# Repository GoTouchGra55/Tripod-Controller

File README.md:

# Tripod (Controller)
A device that works as the brains of a tri-legged hopping robot!

## Overview
Tripod-controller is a 4 layer printed circuit board which is to be used as the computing and instructory brains of a major robot project I've been working on.

The board handles the robot's main control electronics, providing the necessary computing capabilities for its various subsystems both planned and unplanned.

## Design

SEE [SCHEMATICS](KiCAD/Controller.pdf)

## Build Instructions
1. Order the PCB using the provided [files](KiCAD/production).
2. Solder all SMD components according to the schematic and PCB layout.
3. Inspect all solder joints and check for shorts.
4. Connect the peripherals according to the schematic.
5. Flash the firmware and verify all interfaces.
6. Test the power rails before connecting the motors.

## BOM
| Category | Item | Quantity | Supplier | Unit Cost (USD) | Total Cost (USD) | Notes |
|---|---|---:|---|---:|---:|---|
| PCB manufacturing | JLCPCB order | 1 | JLCPCB | $134.68 | $134.68 | JLCPCB order subtotal |
| Shipping | FedEx shipping | 1 | FedEx | $27.19 | $27.19 | Included in the quoted JLCPCB total |
| Passive components | SMD resistors | As required | Daraz | $0.00 | $0.00 | Already owned |
| Passive components | SMD capacitors | As required | Daraz | $0.00 | $0.00 | Already owned |
| **TOTAL** |  |  |  |  | **$161.87** |  |

### SEE [BOM](BOM.csv)

## IMPORTANT
1. Use a 3-4s LiPo battery if you decide to use this board in your project. Discard the battery if it smells "funny".

2. Check for any damage on the pcb as it can be the reason for a catastrophic failure.

## License
MIT-License - SEE [LICENSE](LICENSE)

## Author
Shaurya Tamang  
Contact: [Email](shauryatamand.dev@gmail.com)

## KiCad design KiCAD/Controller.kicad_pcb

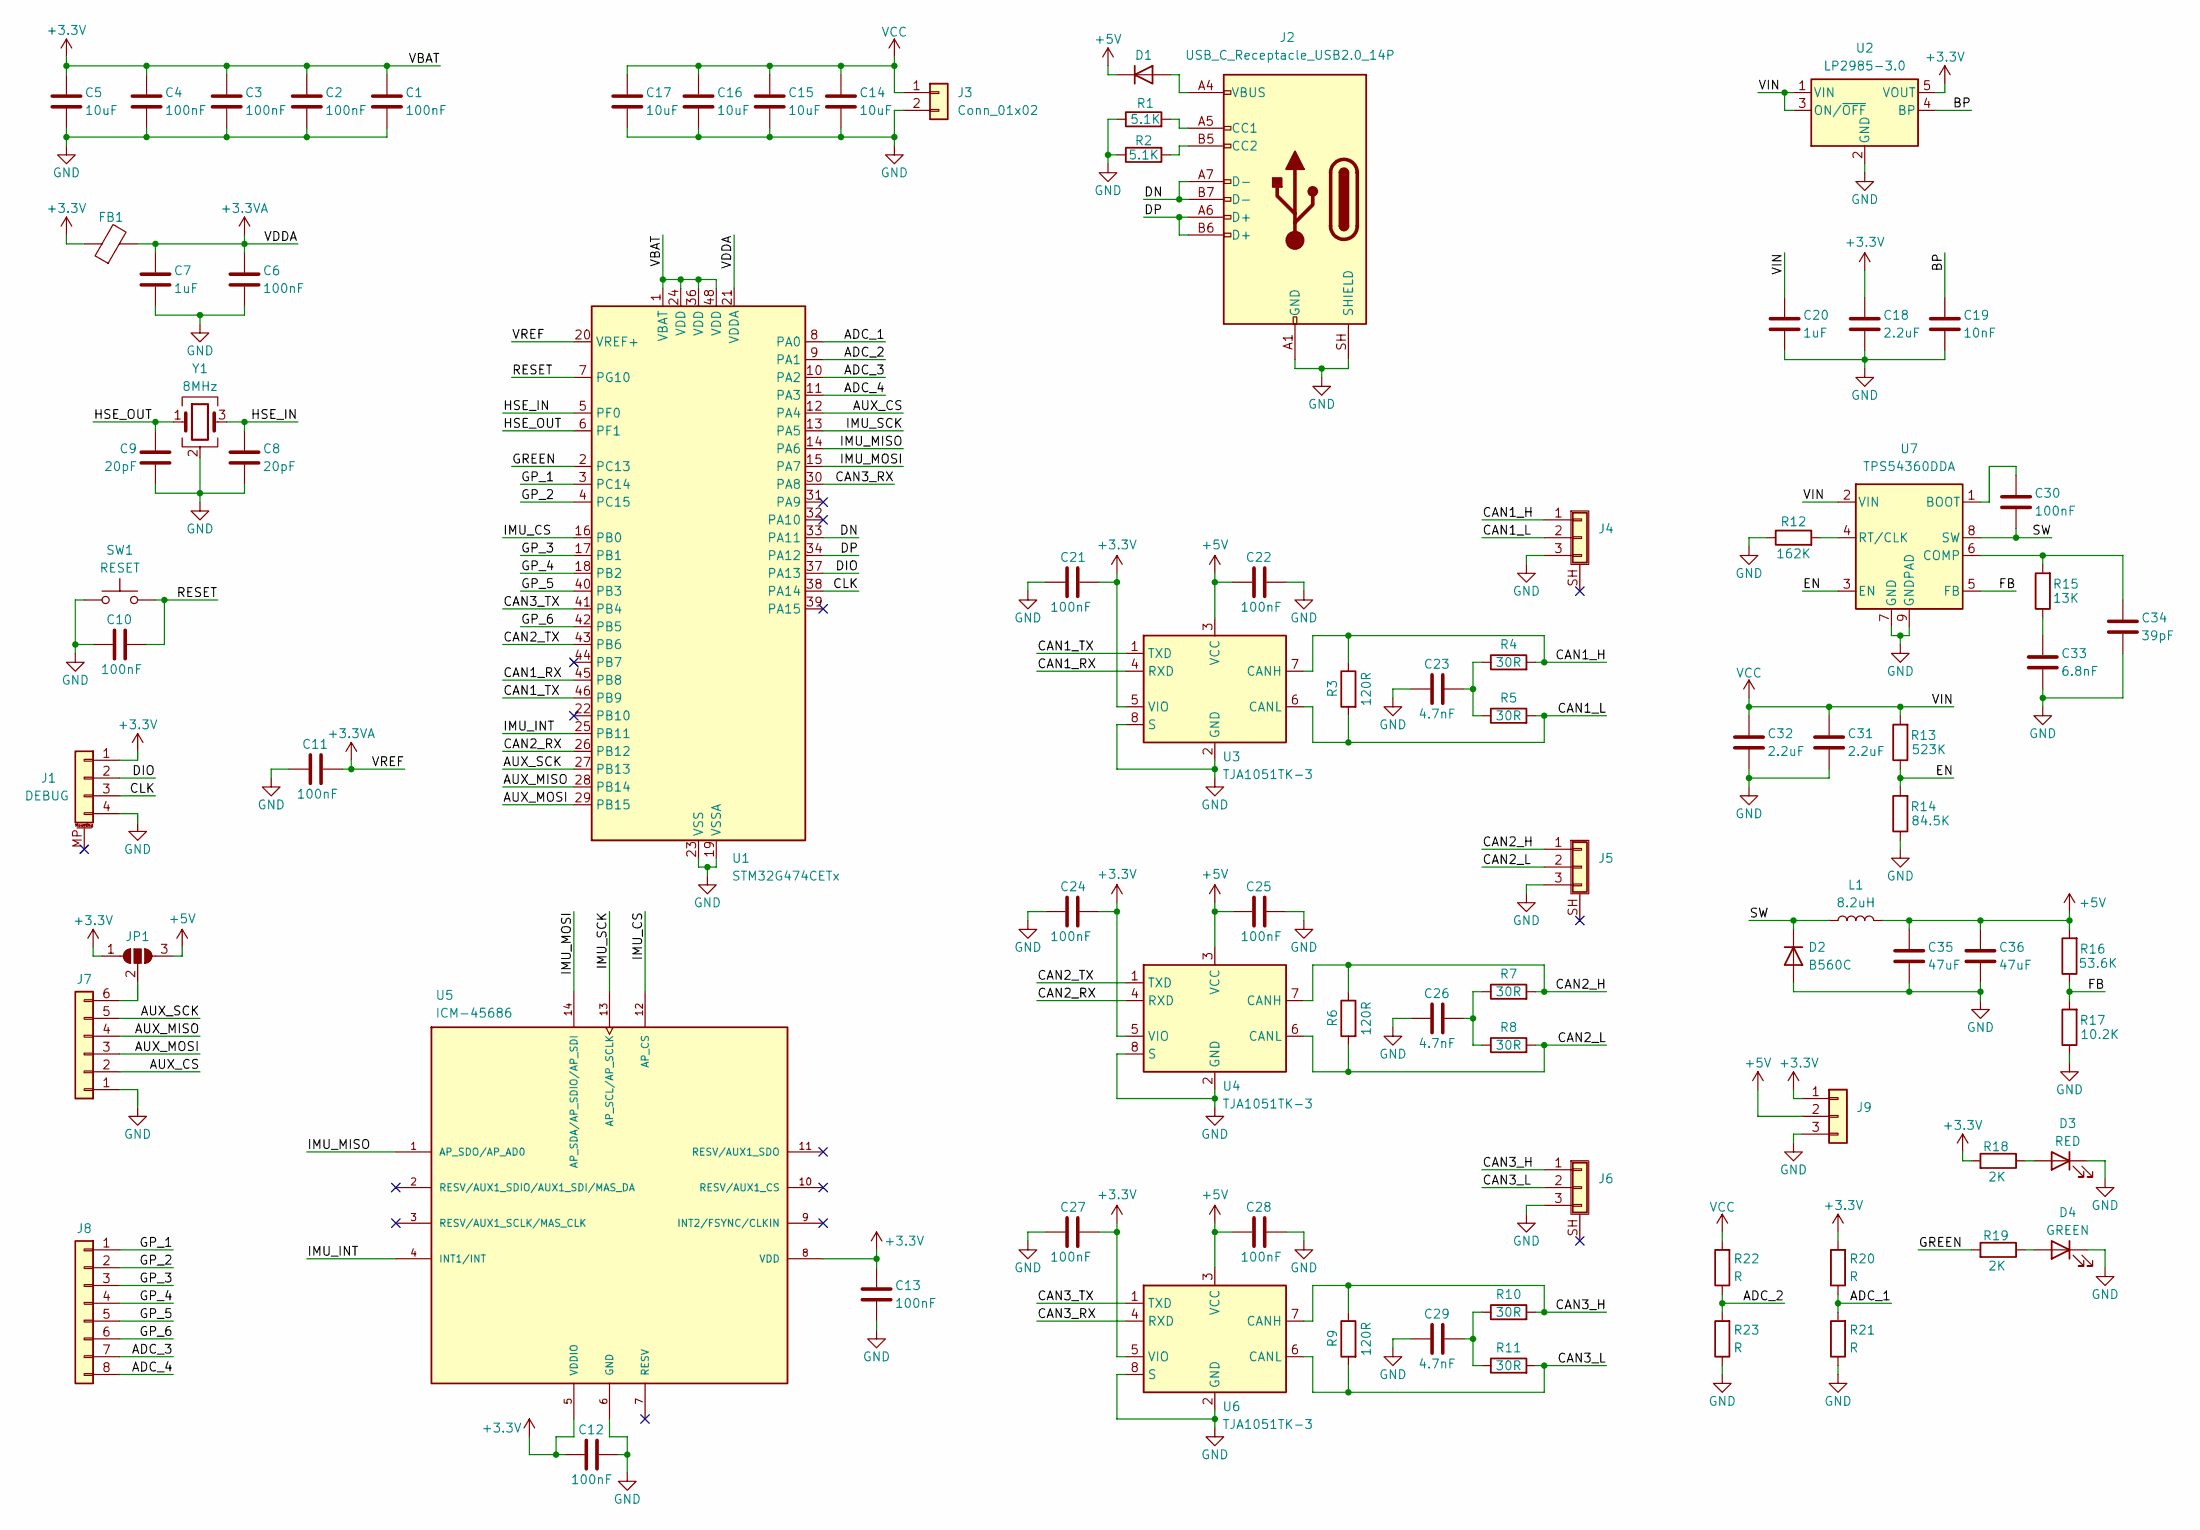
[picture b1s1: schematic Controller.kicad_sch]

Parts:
C1, C2, C3, C4, C6, C10, C11, C12, C13, C21, C22, C24, C25, C27, C28, C30: 100nF; C_0402_1005Metric
C5, C14, C15, C16, C17: 10uF; C_0603_1608Metric
C7, C20: 1uF; C_0603_1608Metric
C8, C9: 20pF; C_0402_1005Metric
C18, C31, C32: 2.2uF; C_0603_1608Metric
C19: 10nF; C_0402_1005Metric
C23, C26, C29: 4.7nF; C_0402_1005Metric
C33: 6.8nF; C_0402_1005Metric
C34: 39pF; C_0402_1005Metric
C35, C36: 47uF; C_0603_1608Metric
D1: D; Nexperia_CFP3_SOD-123W
D2: B560C; Nexperia_CFP3_SOD-123W
D3: RED; D_0603_1608Metric
D4: GREEN; D_0603_1608Metric
FB1: FerriteBead; D_0603_1608Metric
J1: DEBUG; JST_PH_S3B-PH-K_1x03_P2.00mm_Horizontal
J2: USB_C_Receptacle_USB2.0_14P; USB_C_Receptacle_GCT_USB4105-xx-A_16P_TopMnt_Horizontal
J3: Conn_01x02; AMASS_XT60PW-M_1x02_P7.20mm_Horizontal
J4, J5, J6: Conn_01x03_Shielded; JST_PH_S3B-PH-K_1x03_P2.00mm_Horizontal
J7: Conn_01x06; JST_PH_S6B-PH-K_1x06_P2.00mm_Horizontal
J8: Conn_01x08; JST_PH_S8B-PH-K_1x08_P2.00mm_Horizontal
J9: Conn_01x03; JST_PH_S3B-PH-K_1x03_P2.00mm_Horizontal
JP1: SolderJumper_3_Open; SolderJumper-3_P1.3mm_Open_Pad1.0x1.5mm
L1: 8.2uH; L_Cenker_CKCS5040
R1, R2: 5.1K; R_0603_1608Metric
R3, R6, R9: 120R; R_0603_1608Metric
R4, R5, R7, R8, R10, R11: 30R; R_0603_1608Metric
R12: 162K; R_0603_1608Metric
R13: 523K; R_0603_1608Metric
R14: 84.5K; R_0603_1608Metric
R15: 13K; R_0603_1608Metric
R16: 53.6K; R_0603_1608Metric
R17: 10.2K; R_0603_1608Metric
R18, R19: 2K; R_0603_1608Metric
R20, R21, R22, R23: R; R_0603_1608Metric
SW1: RESET; SW_Push_SPST_NO_Alps_SKRK
U1: STM32G474CETx; LQFP-48_7x7mm_P0.5mm
U2: LP2985-3.0; SOT-23-5
U3, U4, U6: TJA1051TK-3; HVSON-8-1EP_3x3mm_P0.65mm_EP1.6x2.4mm
U5: ICM-45686; IC_ICM-45686; PARTREV 0.2
U7: TPS54360DDA; TI_SO-PowerPAD-8_ThermalVias
Y1: 8MHz; Crystal_SMD_3225-4Pin_3.2x2.5mm

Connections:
+3.3V: C1.1, C2.1, C3.1, C4.1, C5.1, C12.2, C13.1, C18.1, C21.1, C24.1, C27.1, FB1.1, J1.1, J9.1, JP1.1 (A), R18.2, R20.2, U1.1 (VBAT), U1.24 (VDD), U1.36 (VDD), U1.48 (VDD), U2.5 (VOUT), U3.5 (VIO), U4.5 (VIO), U5.5 (VDDIO), U5.8 (VDD), U6.5 (VIO)
+3.3VA: C6.1, C7.1, C11.2, FB1.2, U1.20 (VREF+), U1.21 (VDDA)
+5V: C22.1, C25.1, C28.1, C35.1, C36.1, D1.1 (K), J9.2, JP1.3 (B), L1.2, R16.2, U3.3 (VCC), U4.3 (VCC), U6.3 (VCC)
/ADC_1: R20.1, R21.2, U1.8 (PA0)
/ADC_2: R22.1, R23.2, U1.9 (PA1)
/ADC_3: J8.7, U1.10 (PA2)
/ADC_4: J8.8, U1.11 (PA3)
/AUX_CS: J7.2, U1.12 (PA4)
/AUX_MISO: J7.4, U1.28 (PB14)
/AUX_MOSI: J7.3, U1.29 (PB15)
/AUX_SCK: J7.5, U1.27 (PB13)
/BP: C19.1, U2.4 (BP)
/CAN1_H: J4.1, R3.1, R4.2, U3.7 (CANH)
/CAN1_L: J4.2, R3.2, R5.2, U3.6 (CANL)
/CAN1_RX: U1.45 (PB8), U3.4 (RXD)
/CAN1_TX: U1.46 (PB9), U3.1 (TXD)
/CAN2_H: J5.1, R6.1, R7.2, U4.7 (CANH)
/CAN2_L: J5.2, R6.2, R8.2, U4.6 (CANL)
/CAN2_RX: U1.26 (PB12), U4.4 (RXD)
/CAN2_TX: U1.43 (PB6), U4.1 (TXD)
/CAN3_H: J6.1, R9.1, R10.2, U6.7 (CANH)
/CAN3_L: J6.2, R9.2, R11.2, U6.6 (CANL)
/CAN3_RX: U1.30 (PA8), U6.4 (RXD)
/CAN3_TX: U1.41 (PB4), U6.1 (TXD)
/CLK: J1.3, U1.38 (PA14)
/DIO: J1.2, U1.37 (PA13)
/DN: J2.A7 (D-), J2.B7 (D-), U1.33 (PA11)
/DP: J2.A6 (D+), J2.B6 (D+), U1.34 (PA12)
/EN: R13.1, R14.2, U7.3 (EN)
/FB: R16.1, R17.2, U7.5 (FB)
/GP_1: J8.1, U1.3 (PC14)
/GP_2: J8.2, U1.4 (PC15)
/GP_3: J8.3, U1.17 (PB1)
/GP_4: J8.4, U1.18 (PB2)
/GP_5: J8.5, U1.40 (PB3)
/GP_6: J8.6, U1.42 (PB5)
/GREEN: R19.2, U1.2 (PC13)
/HSE_IN: C8.1, U1.5 (PF0), Y1.3
/HSE_OUT: C9.1, U1.6 (PF1), Y1.1
/IMU_CS: U1.16 (PB0), U5.12 (AP_CS)
/IMU_INT: U1.25 (PB11), U5.4 (INT1/INT)
/IMU_MISO: U1.14 (PA6), U5.1 (AP_SDO/AP_AD0)
/IMU_MOSI: U1.15 (PA7), U5.14 (AP_SDA/AP_SDIO/AP_SDI)
/IMU_SCK: U1.13 (PA5), U5.13 (AP_SCL/AP_SCLK)
/RESET: C10.2, SW1.2, U1.7 (PG10)
/SW: C30.2, D2.1 (K), L1.1, U7.8 (SW)
GND: C1.2, C2.2, C3.2, C4.2, C5.2, C6.2, C7.2, C8.2, C9.2, C10.1, C11.1, C12.1, C13.2, C14.2, C15.2, C16.2, C17.2, C18.2, C19.2, C20.2, C21.2, C22.2, C23.1, C24.2, C25.2, C26.1, C27.2, C28.2, C29.1, C31.2, C32.2, C33.2, C34.2, C35.2, C36.2, D2.2 (A), D3.1 (K), D4.1 (K), J1.4, J2.A1 (GND), J2.A12 (GND), J2.B1 (GND), J2.B12 (GND), J2.SH (SHIELD), J3.2, J4.3, J5.3, J6.3, J7.1, J9.3, R1.1, R2.1, R12.1, R14.1, R17.1, R21.1, R23.1, SW1.1, U1.19 (VSSA), U1.23 (VSS), U1.35 (VSS), U1.47 (VSS), U2.2 (GND), U3.2 (GND), U3.8 (S), U3.9 (GND), U4.2 (GND), U4.8 (S), U4.9 (GND), U5.6 (GND), U6.2 (GND), U6.8 (S), U6.9 (GND), U7.7 (GND), U7.9 (GNDPAD), Y1.2 (G), Y1.4 (G)
unnamed: C23.2, R4.1, R5.1
unnamed: C26.2, R7.1, R8.1
unnamed: C29.2, R10.1, R11.1
unnamed: C33.1, R15.1
unnamed: D1.2 (A), J2.A4 (VBUS), J2.A9 (VBUS), J2.B4 (VBUS), J2.B9 (VBUS)
unnamed: D3.2 (A), R18.1
unnamed: D4.2 (A), R19.1
unnamed: J2.A5 (CC1), R1.2
unnamed: J2.B5 (CC2), R2.2
unnamed: J7.6, JP1.2 (C)
unnamed: C30.1, U7.1 (BOOT)
unnamed: C34.1, R15.2, U7.6 (COMP)
unnamed: R12.2, U7.4 (RT/CLK)
VCC: C14.1, C15.1, C16.1, C17.1, C20.1, C31.1, C32.1, J3.1, R13.2, R22.2, U2.1 (VIN), U2.3 (ON/~OFF), U7.2 (VIN)

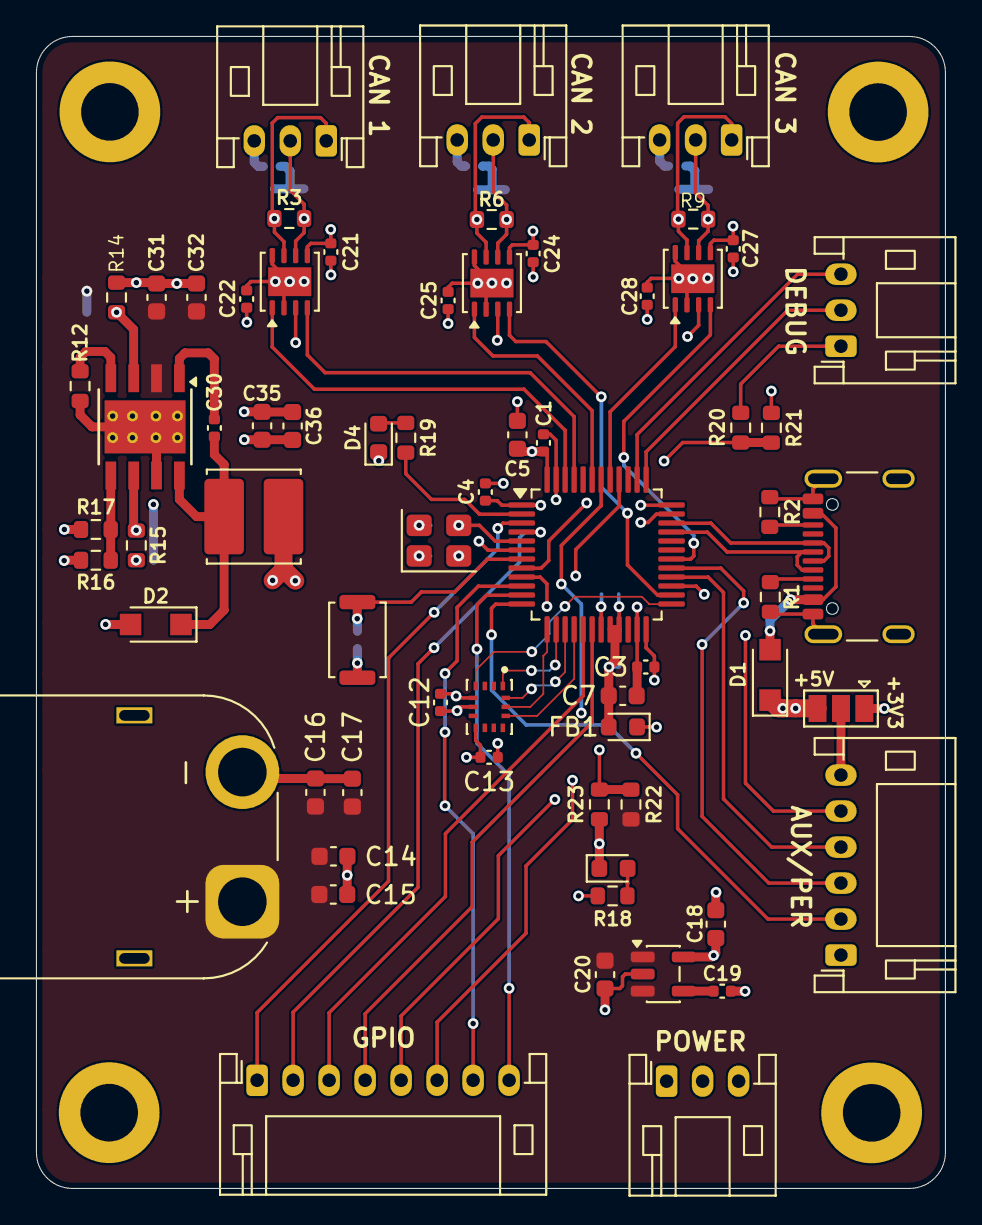
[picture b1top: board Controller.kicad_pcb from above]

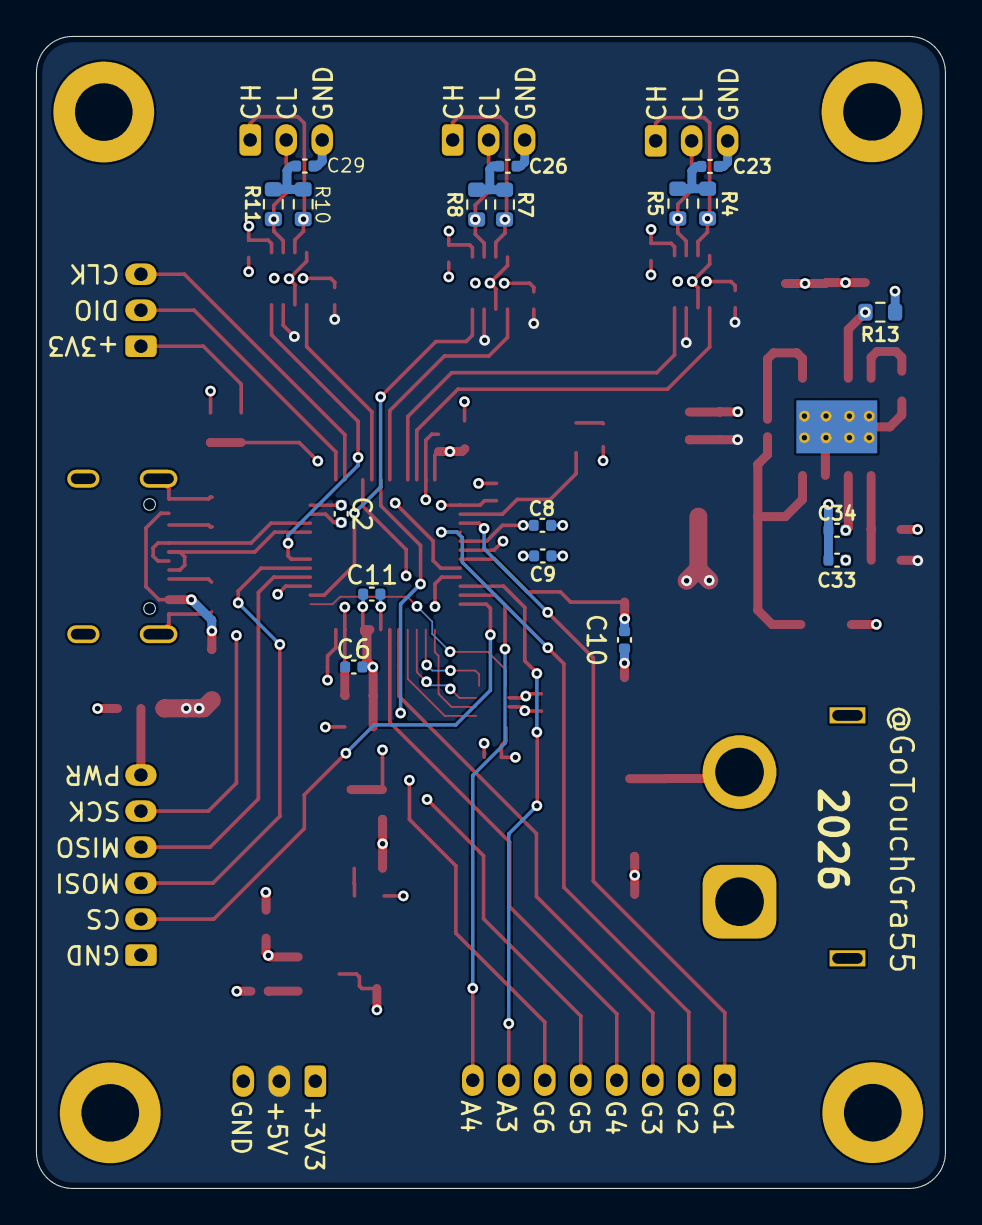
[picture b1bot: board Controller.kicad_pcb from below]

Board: 4 copper layers, 50.5 x 64.0 mm, 84 parts (18 on the bottom side), 61 nets.

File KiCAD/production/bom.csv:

Designator,Footprint,Quantity,Value,LCSC Part #
"C1, C10, C11, C12, C13, C2, C21, C22, C24, C25, C27, C28, C3, C30, C4, C6",0402,16,100nF,
"C14, C15, C16, C17, C5",0603,5,10uF,
"C18, C31, C32",0603,3,2.2uF,
C19,0402,1,10nF,
"C20, C7",0603,2,1uF,
"C23, C26, C29",0402,3,4.7nF,
C33,0402,1,6.8nF,
C34,0402,1,39pF,
"C35, C36",0603,2,47uF,
"C8, C9",0402,2,20pF,
D1,Nexperia_CFP3_SOD-123W,1,D,
D2,Nexperia_CFP3_SOD-123W,1,B560C,
D3,0603,1,RED,
D4,0603,1,GREEN,
FB1,0603,1,FerriteBead,
J1,JST_PH_S3B-PH-K_1x03_P2.00mm_Horizontal,1,DEBUG,
J2,USB_C_Receptacle_GCT_USB4105-xx-A_16P_TopMnt_Horizontal,1,USB_C_Receptacle_USB2.0_14P,
J3,AMASS_XT60PW-M_1x02_P7.20mm_Horizontal,1,Conn_01x02,
"J4, J5, J6",JST_PH_S3B-PH-K_1x03_P2.00mm_Horizontal,3,Conn_01x03_Shielded,
J7,JST_PH_S6B-PH-K_1x06_P2.00mm_Horizontal,1,Conn_01x06,
J8,JST_PH_S8B-PH-K_1x08_P2.00mm_Horizontal,1,Conn_01x08,
J9,JST_PH_S3B-PH-K_1x03_P2.00mm_Horizontal,1,Conn_01x03,
L1,L_Cenker_CKCS5040,1,8.2uH,
"R1, R2",0603,2,5.1K,
"R10, R11, R4, R5, R7, R8",0603,6,30R,
R12,0603,1,162K,
R13,0603,1,523K,
R14,0603,1,84.5K,
R15,0603,1,13K,
R16,0603,1,53.6K,
R17,0603,1,10.2K,
"R18, R19",0603,2,2K,
"R20, R21, R22, R23",0603,4,R,
"R3, R6, R9",0603,3,120R,
SW1,SW_Push_SPST_NO_Alps_SKRK,1,RESET,
U1,LQFP-48_7x7mm_P0.5mm,1,STM32G474CETx,
U2,SOT-23-5,1,LP2985-3.0,
"U3, U4, U6",HVSON-8-1EP_3x3mm_P0.65mm_EP1.6x2.4mm,3,TJA1051TK-3,
U5,IC_ICM-45686,1,ICM-45686,
U7,TI_SO-PowerPAD-8_ThermalVias,1,TPS54360DDA,
Y1,Crystal_SMD_3225-4Pin_3.2x2.5mm,1,8MHz,

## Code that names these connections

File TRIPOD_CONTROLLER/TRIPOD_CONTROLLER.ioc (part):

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Mcu.Name=STM32G474C(B-C-E)Tx
Mcu.Package=LQFP48
Mcu.UserName=STM32G474CETx
PA0.Mode=IN1-Single-Ended
PA0.Signal=ADC1_IN1
PA1.Mode=IN2-Single-Ended
PA1.Signal=ADC1_IN2
PA10.Mode=Asynchronous
PA10.Signal=USART1_RX
PA11.Mode=Device
PA11.Signal=USB_DM
PA12.Mode=Device
PA12.Signal=USB_DP
PA13.Mode=Serial_Wire
PA13.Signal=SYS_JTMS-SWDIO
PA14.Mode=Serial_Wire
PA14.Signal=SYS_JTCK-SWCLK
PA2.Mode=IN3-Single-Ended
PA2.Signal=ADC1_IN3
PA3.Mode=IN4-Single-Ended
PA3.Signal=ADC1_IN4
PA5.GPIOParameters=GPIO_Label
PA5.GPIO_Label=IMU_SCK
PA5.Mode=Full_Duplex_Master
PA5.Signal=SPI1_SCK
PA6.GPIOParameters=GPIO_Label
PA6.GPIO_Label=IMU_MISO
PA6.Mode=Full_Duplex_Master
PA6.Signal=SPI1_MISO
PA7.GPIOParameters=GPIO_Label
PA7.GPIO_Label=IMU_MOSI
PA7.Mode=Full_Duplex_Master
PA7.Signal=SPI1_MOSI
PA8.Mode=FDCAN_Activate
PA8.Signal=FDCAN3_RX
PA9.Mode=Asynchronous
PA9.Signal=USART1_TX
PB0.GPIOParameters=GPIO_Label
PB0.GPIO_Label=IMU_CS
PB0.Signal=GPIO_Output
PB1.GPIOParameters=GPIO_Label
PB1.GPIO_Label=AUX_CS
PB1.Signal=GPIO_Output
PB12.Mode=FDCAN_Activate
PB12.Signal=FDCAN2_RX
PB13.GPIOParameters=GPIO_Label
PB13.GPIO_Label=AUX_SCK
PB13.Mode=Full_Duplex_Master
PB13.Signal=SPI2_SCK
PB14.GPIOParameters=GPIO_Label
PB14.GPIO_Label=AUX_MISO
PB14.Mode=Full_Duplex_Master
PB14.Signal=SPI2_MISO
PB15.GPIOParameters=GPIO_Label
PB15.GPIO_Label=AUX_MOSI
PB15.Mode=Full_Duplex_Master
PB15.Signal=SPI2_MOSI
PB4.Mode=FDCAN_Activate
PB4.Signal=FDCAN3_TX
PB6.Mode=FDCAN_Activate
PB6.Signal=FDCAN2_TX
PB8-BOOT0.Mode=FDCAN_Activate
PB8-BOOT0.Signal=FDCAN1_RX
PB9.Mode=FDCAN_Activate
PB9.Signal=FDCAN1_TX
PF0-OSC_IN.Mode=HSE-External-Oscillator
PF0-OSC_IN.Signal=RCC_OSC_IN
PF1-OSC_OUT.Mode=HSE-External-Oscillator
PF1-OSC_OUT.Signal=RCC_OSC_OUT
RCC.HSE_VALUE=16000000
RCC.SYSCLKFreq_VALUE=144000000
RCC.SYSCLKSource=RCC_SYSCLKSOURCE_PLLCLK
board=custom
